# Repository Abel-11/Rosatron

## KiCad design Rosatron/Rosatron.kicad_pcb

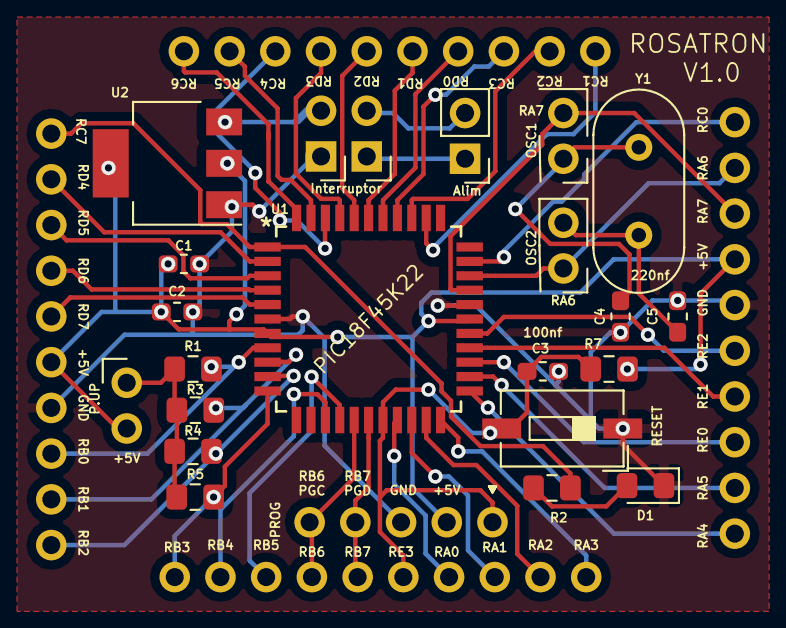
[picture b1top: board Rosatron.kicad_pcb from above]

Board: 2 copper layers, 22 parts (0 on the bottom side), 17 nets.

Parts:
 : C; C_0603_1608Metric_Pad1.05x0.95mm_HandSolder
Alim: Conn_01x02_Male; PinHeader_1x02_P2.54mm_Vertical
C1, C2, C3, C5: C; C_0603_1608Metric_Pad1.05x0.95mm_HandSolder
D1: LED; LED_0805_2012Metric_Pad1.15x1.40mm_HandSolder
Interruptor: Conn_01x02_Male; PinHeader_1x02_P2.54mm_Vertical
OSC1, OSC2: Conn_01x02_Male; PinHeader_1x02_P2.54mm_Vertical
P.UP: Conn_01x02_Male; PinHeader_1x02_P2.54mm_Vertical
PROG: PinHeader_1x05_P2.54mm_Vertical
R1, R3, R4, R5, R7: 1k; R_0805_2012Metric_Pad1.15x1.40mm_HandSolder
R2: 330R; R_0805_2012Metric_Pad1.15x1.40mm_HandSolder
RESET: SW_SPST; SW_DIP_SPSTx01_Slide_6.7x4.1mm_W6.73mm_P2.54mm_LowProfile_J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
U1: PIC18F45K22; pic18f45k22-i&slash_pt
U2: AMS1117-5.0; SOT-223-3_TabPin2
Y1: Crystal; Crystal_HC49-U_Vertical

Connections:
+5V: C1.1, C2.1, P.UP.2, PROG.2, R7.2, U1.7, U1.28, U2.2
/RA6: OSC2.1, U1.31
/RA7: OSC1.2, U1.30
/RB0: R1.2, U1.8
/RB1: R3.2, U1.9
/RB2: R4.2, U1.10
/RB3: R5.2, U1.11
/RB6_PGC: PROG.5, U1.16
/RB7_PGD: PROG.4, U1.17
/RC7: R2.2, U1.1
/RE3_MCLR: C3.1, PROG.1, R7.1, RESET.2, U1.18
Earth: .2, C1.2, C2.2, C3.2, C5.2, D1.1, Interruptor.1, PROG.3, RESET.1, U1.6, U1.29, U2.1
unnamed: C5.1, OSC1.1, Y1.1
unnamed: .1, OSC2.2, Y1.2
unnamed: D1.2, R2.1
unnamed: Interruptor.2, U2.3
unnamed: P.UP.1, R1.1, R3.1, R4.1, R5.1

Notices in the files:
parts and their libraries:
Copyright 2016 Accelerated Designs. All rights reserved.
